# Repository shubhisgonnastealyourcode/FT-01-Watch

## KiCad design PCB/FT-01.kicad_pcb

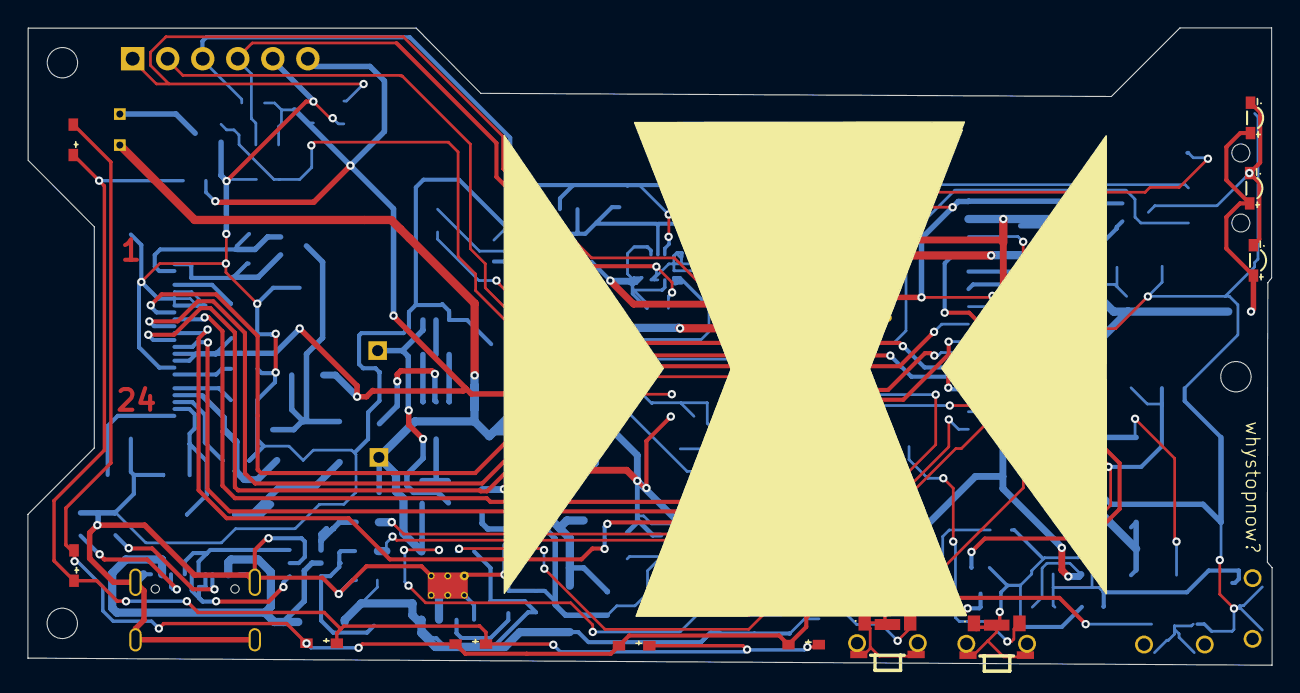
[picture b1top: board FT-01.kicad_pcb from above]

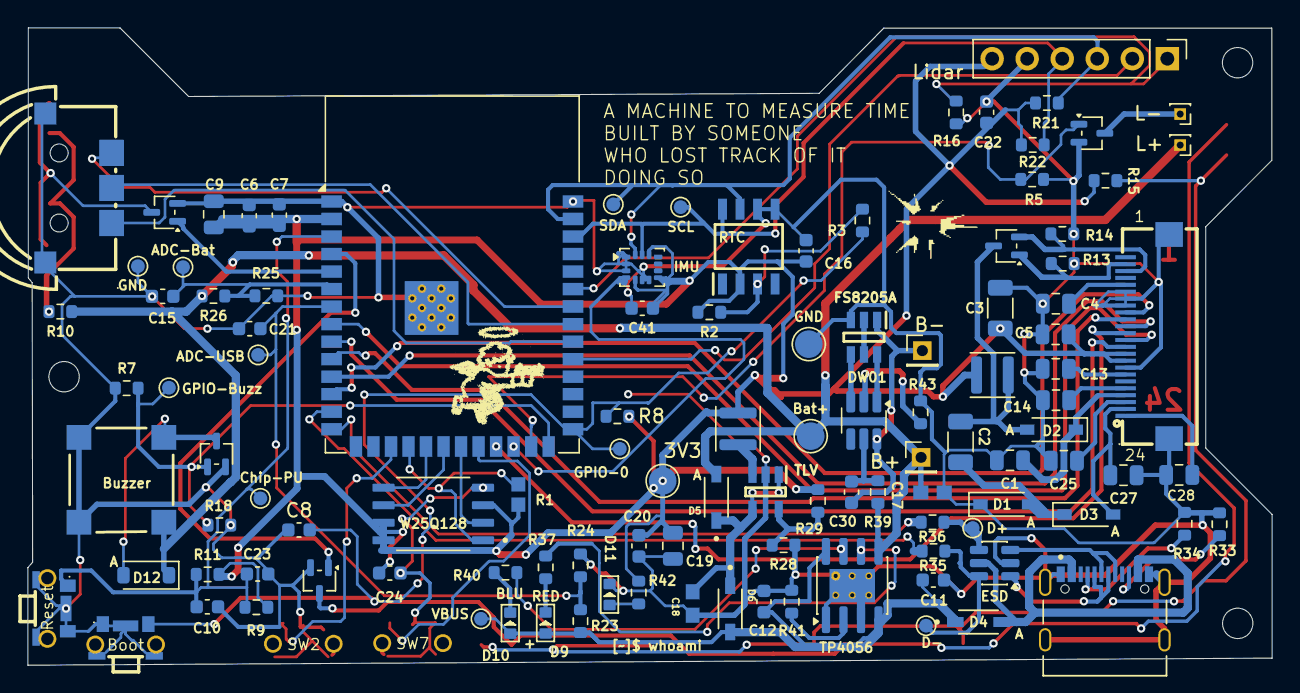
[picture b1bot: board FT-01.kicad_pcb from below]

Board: 2 copper layers, 90.2 x 46.2 mm, 123 parts (112 on the bottom side), 73 nets.

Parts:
3V3: 3V3; TestPoint_Pad_D2.0mm
ADC-Bat: ADC_Bat; TestPoint_Pad_D1.0mm
ADC-USB: ADC_USB; TestPoint_Pad_D1.0mm
B+: TestPoint; PinHeader_1x01_P2.00mm_Vertical
B-1: TestPoint; PinHeader_1x01_P2.00mm_Vertical
Bat+: P+; TestPoint_Pad_D2.0mm
C1, C4, C5, C13, C14, C25, C27, C28: 1uF/25V; C_0805_2012Metric
C2, C3: 4.7uF/25V; C_1206_3216Metric
C6, C11, C12: 10uF; C_0603_1608Metric
C7, C8, C15, C16, C20, C21, C22, C23, C24, C30, C41: 100nF; C_0603_1608Metric
C9, C19: 22uF; C_0805_2012Metric
C10: 1uF; C_0603_1608Metric
C17, C18: 10uF; CAPC1608X90
Chip-PU: Reset; TestPoint_Pad_D1.0mm
D1, D2, D3: MBR0530; SOD123
D4, D5, D6: 1N5819HW-7-F; SOD3715X145N
D9: SMD BLUE; LED-0603
D10, D11: SMD RED; LED-0603
D12: 1N4148WS; D_SOD-123
D+: D+; TestPoint_Pad_D1.0mm
D-: D-; TestPoint_Pad_D1.0mm
DW01: DW01A; SOT-23-6_Handsoldering
ESD: USBLC6-2SC6; SOT-23-6
FPC: AFC24-S24FIA-00; FPC-SMD_P0.50-24P_QCHF-SM-H2.0
FS8205A: FS8205A; SOT95P280X125-6N
GND: P-; TestPoint_Pad_D2.0mm
GND#2: GND; TestPoint_Pad_D1.0mm
GPIO-0: Boot; TestPoint_Pad_D1.0mm
GPIO-Buzz: BUZZ; TestPoint_Pad_D1.0mm
J3: TYPE-C-31-M-12; HRO_TYPE-C-31-M-12
L1: 47uH 500mA; L_APV_ANR3015
L3: 2.2uH; L_APV_ANR3015
L+: TestPoint; PinHeader_1x01_P1.00mm_Vertical
L-: TestPoint; PinHeader_1x01_P1.00mm_Vertical
LS2: CMT-7525-80-SMT-TR; CMT752580SMTTR
Lidar: Conn_01x06_Pin; PinHeader_1x06_P2.54mm_Vertical
Q2, Q4, Q5, Q6, Q8: Si1308EDL; SOT-323_SC-70
R1: 10k; RESC1607X60N
R2: 10k; R_0603_1608Metric
R3: 0R; R_0603_1608Metric
R5, R7, R8, R9, R16, R18: 10K; R_0603_1608Metric
R10: 22R; R_0603_1608Metric
R11, R33, R34: 5k1; R_0603_1608Metric
R13: 1M; R_0603_1608Metric
R14: 2R2; R_0603_1608Metric
R15: 47R; R_0603_1608Metric
R21, R22, R23: 4k7; R_0603_1608Metric
R24, R25, R26, R28: 100k; R_0603_1608Metric
R29: 450K; R_0603_1608Metric
R35, R36: 27R; R_0603_1608Metric
R37, R39, R40: 1k; R_0603_1608Metric
R41: 3K; R_0603_1608Metric
R42: 1K; R_0603_1608Metric
R43: 2K2; R_0603_1608Metric
RTC: DS3231MZ_V+T; SOIC127P600X175-8N
SCL: SCL; TestPoint_Pad_D1.0mm
SDA: SDA; TestPoint_Pad_D1.0mm
SW1, SW2: KEY-SMD_TS24ZJ-1
SW5: K1-1502SA-01; KEY-SMD_K1-1502SA-01
SW7, SW8: TS24ZJ; KEY-SMD_TS24ZJ-1
TLV: TLV62566DBVR; SOT95P280X145-5N
TP4056: TP4056-42-ESOP8; SOIC-8-1EP_3.9x4.9mm_P1.27mm_EP2.41x3.3mm_ThermalVias
U4: LSM6DSL; LGA-14_3x2.5mm_P0.5mm_LayoutBorder3x4y
U5: ESP32-S3-WROOM-1
U6: W25Q128JVSIQ; SOIC127P790X216-8N
U12, U12#2, U12#3, U12#4, U12#5, U12#6, U13, U14, U15: XL-2106UWC; LED-SMD_L2.1-W1.0-RD_RED
VBUS: VBUS; TestPoint_Pad_D1.0mm

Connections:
+3.3V: 3V3.1 (1_1), C3.1, C5.2, C6.2, C7.2, C9.2, C16.2, C19.2, C20.2, C22.2, C24.1, C41.1, FPC.9, FPC.10, L1.1, L3.2, Lidar.6, R1.2, R2.2, R8.2, R9.2, R11.2, R15.2, R21.1, R22.1, R29.1, R42.1, RTC.2 (VCC), U4.5 (VDDIO), U4.8 (VDD), U4.12 (CS), U5.2 (3V3), U6.3 (/WP(IO2)), U6.7 (/HOLD/RESET(IO3)), U6.8 (VCC)
ADC_Bat: ADC-Bat.1 (1_1), C15.2, R25.2, R26.1, U5.6 (IO6)
ADC_USB: ADC-USB.1 (1_1), C21.2, R23.1, R24.2, U5.7 (IO7)
BUSY: FPC.16, U5.12 (IO8)
CHIP_PU: C10.1, C23.2, Chip-PU.1 (1_1), R9.1, R11.1, SW2.1, U5.3 (EN)
CS#: FPC.13, U5.23 (IO21)
D+: R36.1, U5.14 (USB_D+)
D-: R35.1, U5.13 (USB_D-)
DI(IO0): U5.19 (IO11), U6.5 (DI(IO0))
DO(IO1): U5.21 (IO13), U6.2 (DO(IO1))
D/C#: FPC.14, U5.11 (IO18)
FLASH: Q4.1 (G), U5.5 (IO5)
Frontlight: Q5.1 (G), U5.4 (IO4)
GDR: FPC.23, Q2.1 (G), R13.1
GND: C1.2, C3.2, C4.1, C5.1, C6.1, C7.1, C8.1, C9.1, C10.2, C11.2, C12.1, C13.1, C14.1, C15.1, C16.1, C17.2, C18.1, C19.1, C20.1, C21.1, C22.1, C23.1, C24.2, C25.1, C27.1, C28.1, C41.2, D1.C, D11.-, ESD.2 (GND), FPC.8, FPC.17, FPC.18, FPC.19, FPC.25, FPC.26, FS8205A.3 (S2), GND.1 (1_1), GND#2.1 (1_1), J3.A1_B12 (GND), J3.B1_A12 (GND), J3.S1 (SHIELD), J3.S2 (SHIELD), J3.S3 (SHIELD), J3.S4 (SHIELD), LS2.3 (DUMMY_1), LS2.4 (DUMMY_2), Lidar.5, Q4.2 (S), Q5.2 (S), Q6.2 (S), Q8.2 (S), R5.2, R7.1, R13.2, R14.2, R16.1, R18.1, R24.1, R25.1, R28.2, R33.1, R34.1, R41.1, R43.1, RTC.5 (GND), RTC.6 (VBAT), SW1.1, SW1.3, SW1.4, SW1.5, SW2.2, SW2.3, SW2.4, SW2.5, SW5.5, SW5.C, SW7.1, SW7.3, SW7.4, SW7.5, SW8.1, SW8.3, SW8.4, SW8.5, TLV.2 (GND), TP4056.1 (TEMP), TP4056.3 (GND), TP4056.9 (EPAD), U4.1 (SDO/SA0), U4.2 (SDX), U4.3 (SCX), U4.6 (GND), U4.7 (GND), U5.1 (GND), U5.40 (GND), U5.41 (GND), U6.4 (GND)
GPIO0: C8.2, GPIO-0.1 (1_1), R3.2, R8.1, SW1.2, U5.27 (IO0)
IMU_GPIO: Lidar.2, U5.31 (IO38)
IMU_GPIO_XSHUT: Lidar.1, R16.2, U5.35 (IO42)
IN1_IMU: U4.4 (INT1), U5.24 (IO47)
L+: B+.1 (1_1), Bat+.1 (1_1), C17.1, D5.A, D12.1 (K), L+.1 (1_1), LS2.1 (+), R10.1, R26.2, R39.1, TP4056.5 (BAT)
L-: L-.1 (1_1), Q6.3 (D)
MEM_CLK: U5.20 (IO12), U6.6 (CLK)
MEM_CS: R1.1, U5.18 (IO10), U6.1 (/CS)
unnamed: C2.1, D1.A, D3.C
unnamed: C4.2, FPC.20
unnamed: C13.2, FPC.7
unnamed: C14.2, FPC.5
unnamed: C25.2, FPC.3
unnamed: C28.2, FPC.1
unnamed: D9.-, R40.2
unnamed: D10.-, R37.2
unnamed: D11.+, R42.2
unnamed: D12.2 (A), LS2.2 (-), Q8.3 (D)
unnamed: C18.2, D5.C, D6.C, TLV.1 (EN/PG), TLV.4 (VIN)
unnamed: R28.1, R29.2, TLV.5 (FB)
unnamed: L3.1, TLV.3 (SW)
unnamed: R2.1, R3.1, RTC.3 (~INT/SQW)
unnamed: J3.A5 (CC1), R34.2
unnamed: J3.B5 (CC2), R33.2
unnamed: ESD.1 (I/O1), J3.A7 (DN1), J3.B7 (DN2)
unnamed: ESD.3 (I/O2), J3.A6 (DP1), J3.B6 (DP2)
unnamed: C2.2, D2.A, L1.2, Q2.3 (D)
unnamed: Q4.3 (D), U13.1 (-), U14.1 (-), U15.1 (-)
unnamed: Q5.3 (D), U12#2.1 (-)
unnamed: FS8205A.2 (D1/D2_1), FS8205A.5 (D1/D2_2)
unnamed: DW01.1 (OD), FS8205A.6 (G1)
unnamed: DW01.3 (OC), FS8205A.4 (G2)
unnamed: B-1.1 (1_1), C30.2, DW01.6 (GND), FS8205A.1 (S1)
unnamed: D-.1 (1_1), ESD.6 (I/O1), R35.2
unnamed: D+.1 (1_1), ESD.4 (I/O2), R36.2
unnamed: R41.2, TP4056.2 (PROG)
unnamed: R40.1, TP4056.7 (~CHRG)
unnamed: R37.1, TP4056.6 (~STDBY)
unnamed: R15.1, U12#2.2 (+)
unnamed: R10.2, U13.2 (+), U14.2 (+), U15.2 (+)
unnamed: DW01.2 (CS), R43.2
unnamed: C30.1, DW01.5 (VCC), R39.2
RES#: FPC.15, U5.10 (IO17)
RESE: FPC.22, Q2.2 (S), R14.1
SCL: Lidar.4, R22.2, RTC.8 (SCL), SCL.1 (1_1), U4.13 (SCL), U5.38 (IO2)
SCL_D: FPC.12, U5.8 (IO15)
SDA: Lidar.3, R21.2, RTC.7 (SDA), SDA.1 (1_1), U4.14 (SDA), U5.39 (IO1)
SDA_D: FPC.11, U5.9 (IO16)
SW_1: SW8.2, U5.17 (IO9)
SW_2: SW7.2, U5.22 (IO14)
SW_C: SW5.T, U5.33 (IO40)
SW_D: SW5.2, U5.34 (IO41)
SW_U: SW5.1, U5.32 (IO39)
VBUS: C11.1, C12.2, D4.A, D4.C, D6.A, D9.+, D10.+, ESD.5 (VBUS), J3.A4_B9 (VBUS), J3.B4_A9 (VBUS), R23.2, TP4056.4 (V_{CC}), TP4056.8 (CE), VBUS.1 (1_1)
VGH: C1.1, D2.C, FPC.4
VGL: C27.2, D3.A, FPC.2
buzzer_gpio: GPIO-Buzz.1 (1_1), Q8.1 (G), R7.2, R18.2, U5.26 (IO45)
laser_gpio: Q6.1 (G), R5.1, U5.25 (IO48)

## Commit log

2026-04-22 Add initial README for Schematic and PCB
